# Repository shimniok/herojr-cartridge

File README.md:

# Hero Jr cartridge

Eagle schematics and board layouts for Heathkit Hero Jr cartridge

The Hero Jr maps cartridge ROM to $6000-$8000

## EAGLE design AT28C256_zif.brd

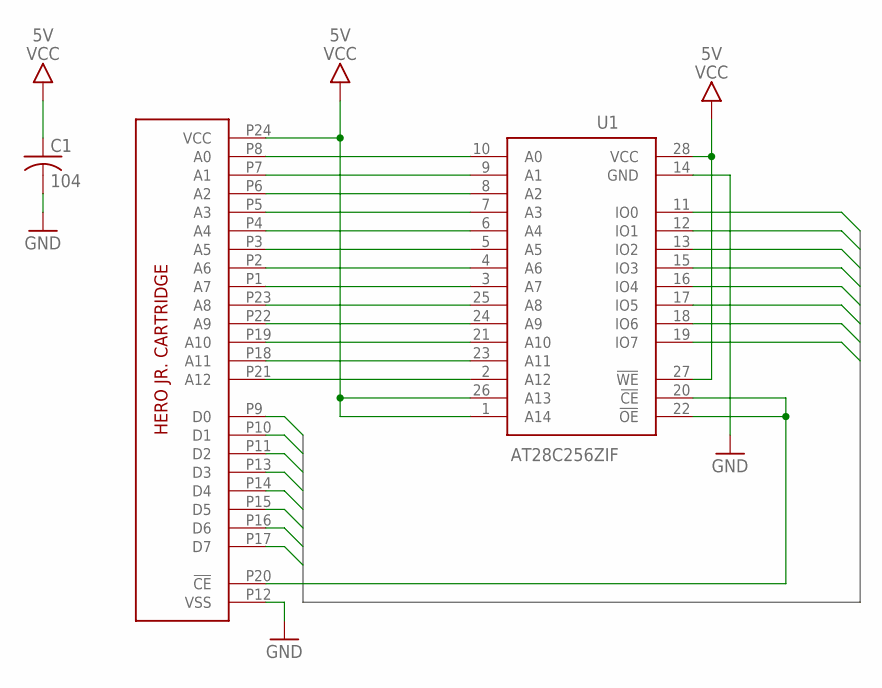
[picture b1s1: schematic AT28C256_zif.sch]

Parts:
C1: 104; C050-025X075
U1: AT28C256ZIF; DIL28-ZIF
U$1: HEROJRCART

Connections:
!CE: U1.20 (!CE), U1.22 (!OE), U$1.P20 (!CE)
A0: U1.10 (A0), U$1.P8 (A0)
A1: U1.9 (A1), U$1.P7 (A1)
A2: U1.8 (A2), U$1.P6 (A2)
A3: U1.7 (A3), U$1.P5 (A3)
A4: U1.6 (A4), U$1.P4 (A4)
A5: U1.5 (A5), U$1.P3 (A5)
A6: U1.4 (A6), U$1.P2 (A6)
A7: U1.3 (A7), U$1.P1 (A7)
A8: U1.25 (A8), U$1.P23 (A8)
A9: U1.24 (A9), U$1.P22 (A9)
A10: U1.21 (A10), U$1.P19 (A10)
A11: U1.23 (A11), U$1.P18 (A11)
A12: U1.2 (A12), U$1.P21 (A12)
D0: U1.11 (IO0), U$1.P9 (D0)
D1: U1.12 (IO1), U$1.P10 (D1)
D2: U1.13 (IO2), U$1.P11 (D2)
D3: U1.15 (IO3), U$1.P13 (D3)
D4: U1.16 (IO4), U$1.P14 (D4)
D5: U1.17 (IO5), U$1.P15 (D5)
D6: U1.18 (IO6), U$1.P16 (D6)
D7: U1.19 (IO7), U$1.P17 (D7)
GND: C1.2, U1.14 (GND), U$1.P12 (VSS)
VCC: C1.1, U1.1 (A14), U1.26 (A13), U1.27 (!WE), U1.28 (VCC), U$1.P24 (VCC)

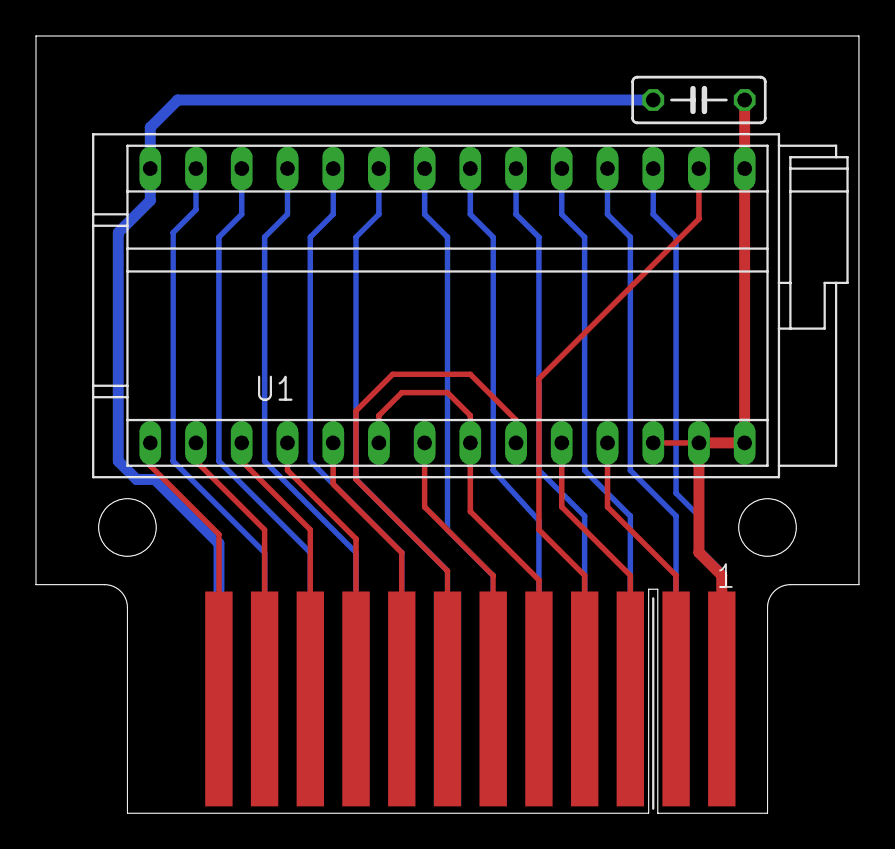
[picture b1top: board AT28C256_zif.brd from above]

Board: 2 copper layers, 45.7 x 43.2 mm, 3 parts (0 on the bottom side), 24 nets.

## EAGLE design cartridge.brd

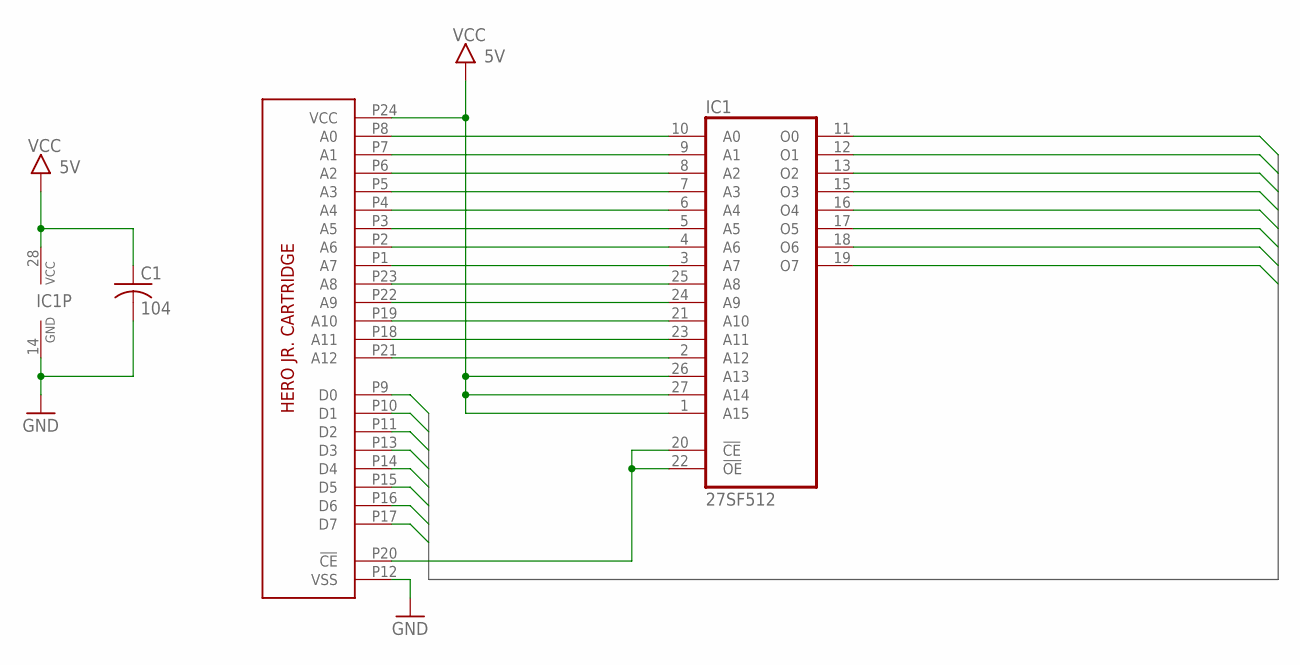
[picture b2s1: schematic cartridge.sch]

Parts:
C1: 104; C050-024X044
IC1: 27SF512; DIL28
U$1: HEROJRCART

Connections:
D0: IC1.11 (O0), U$1.P9 (D0)
D1: IC1.12 (O1), U$1.P10 (D1)
D2: IC1.13 (O2), U$1.P11 (D2)
D3: IC1.15 (O3), U$1.P13 (D3)
D4: IC1.16 (O4), U$1.P14 (D4)
D5: IC1.17 (O5), U$1.P15 (D5)
D6: IC1.18 (O6), U$1.P16 (D6)
D7: IC1.19 (O7), U$1.P17 (D7)
GND: C1.2, IC1.14 (GND), U$1.P12 (VSS)
unnamed: IC1.20 (!CE), IC1.22 (!OE), U$1.P20 (!CE)
unnamed: IC1.10 (A0), U$1.P8 (A0)
unnamed: IC1.9 (A1), U$1.P7 (A1)
unnamed: IC1.8 (A2), U$1.P6 (A2)
unnamed: IC1.7 (A3), U$1.P5 (A3)
unnamed: IC1.6 (A4), U$1.P4 (A4)
unnamed: IC1.5 (A5), U$1.P3 (A5)
unnamed: IC1.4 (A6), U$1.P2 (A6)
unnamed: IC1.3 (A7), U$1.P1 (A7)
unnamed: IC1.25 (A8), U$1.P23 (A8)
unnamed: IC1.24 (A9), U$1.P22 (A9)
unnamed: IC1.21 (A10), U$1.P19 (A10)
unnamed: IC1.23 (A11), U$1.P18 (A11)
unnamed: IC1.2 (A12), U$1.P21 (A12)
VCC: C1.1, IC1.1 (A15), IC1.26 (A13), IC1.27 (A14), IC1.28 (VCC), U$1.P24 (VCC)

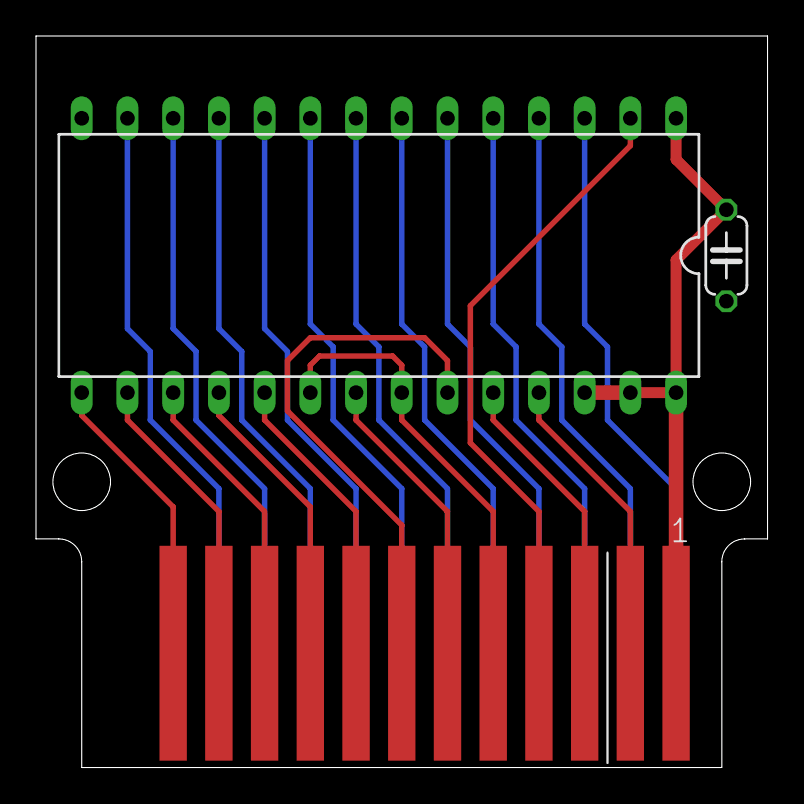
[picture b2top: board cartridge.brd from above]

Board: 2 copper layers, 40.6 x 40.6 mm, 3 parts (0 on the bottom side), 24 nets.

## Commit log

2021-01-05 initial
2021-01-05 Create LICENSE
2021-01-05 initial release for 27512 prom
2021-01-07 Added AT28C256 ZIF version
